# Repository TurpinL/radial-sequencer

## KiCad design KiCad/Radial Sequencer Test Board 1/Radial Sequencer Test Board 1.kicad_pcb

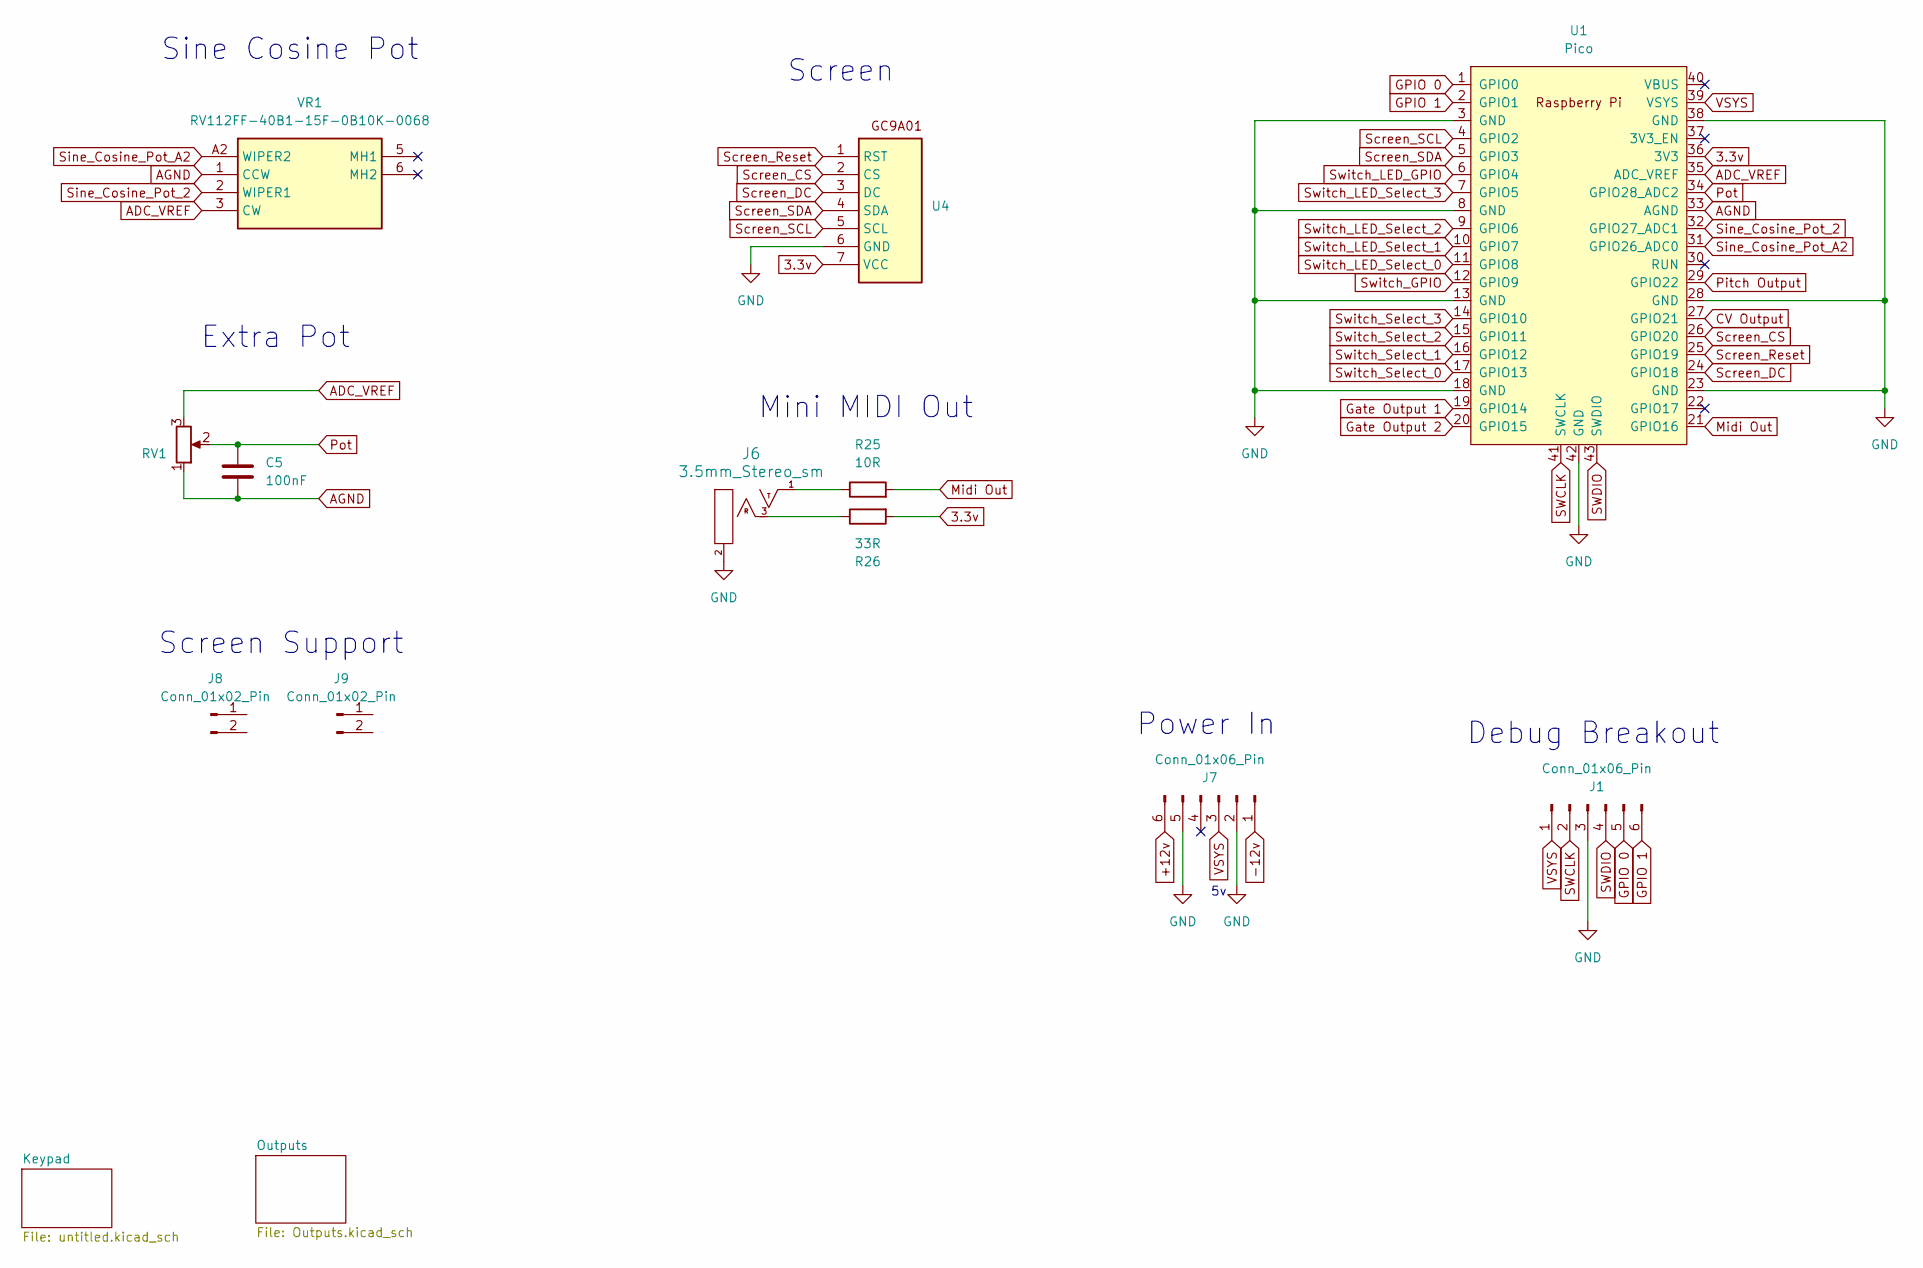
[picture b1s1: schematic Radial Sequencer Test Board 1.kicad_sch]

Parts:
C5: 100nF; C_0805_2012Metric_Pad1.18x1.45mm_HandSolder
J1, J7: Conn_01x06_Pin; PinHeader_1x06_P2.54mm_Vertical
J6: 3.5mm_Stereo_sm; EighthInch_Stereo_PJ366ST; Part Number WQP-WQP518MA
J8, J9: Conn_01x02_Pin; PinHeader_1x02_P2.00mm_Vertical
R25: 10R; R_0805_2012Metric_Pad1.20x1.40mm_HandSolder
R26: 33R; R_0805_2012Metric_Pad1.20x1.40mm_HandSolder
RV1: R_Potentiometer; Potentiometer_Alpha_RD901F-40-00D_Single_Vertical
U1: Pico; RPi_Pico_SMD_TH
U4: PinHeader_1x07_P2.00mm_Vertical
VR1: RV112FF-40B1-15F-0B10K-0068; RV112FF40B115F0B20K0068; Mouser Part Number 317-1240FF-15F-0B20K

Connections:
3.3v: R26.2, U1.36 (3V3), U4.7 (VCC); also elsewhere on the board
+12v: J7.6; also elsewhere on the board
-12v: J7.1; also elsewhere on the board
ADC_VREF: RV1.3, U1.35 (ADC_VREF), VR1.3 (CW)
AGND: C5.2, RV1.1, U1.33 (AGND), VR1.1 (CCW)
CV Output: U1.27 (GPIO21); also elsewhere on the board
GND: J1.3, J6.2 (SHEILD), J7.2, J7.5, U1.3 (GND), U1.8 (GND), U1.13 (GND), U1.18 (GND), U1.23 (GND), U1.28 (GND), U1.38 (GND), U1.42 (GND), U4.6 (GND); also elsewhere on the board
GPIO 0: J1.5, U1.1 (GPIO0)
GPIO 1: J1.6, U1.2 (GPIO1)
Gate Output 1: U1.19 (GPIO14); also elsewhere on the board
Gate Output 2: U1.20 (GPIO15); also elsewhere on the board
Midi Out: R25.2, U1.21 (GPIO16)
unnamed: J6.1 (SIG), R25.1
unnamed: J6.3 (SW), R26.1
Pitch Output: U1.29 (GPIO22); also elsewhere on the board
Pot: C5.1, RV1.2, U1.34 (GPIO28_ADC2)
SWCLK: J1.2, U1.41 (SWCLK)
SWDIO: J1.4, U1.43 (SWDIO)
Screen_CS: U1.26 (GPIO20), U4.2 (CS)
Screen_DC: U1.24 (GPIO18), U4.3 (DC)
Screen_Reset: U1.25 (GPIO19), U4.1 (RST)
Screen_SCL: U1.4 (GPIO2), U4.5 (SCL)
Screen_SDA: U1.5 (GPIO3), U4.4 (SDA)
Sine_Cosine_Pot_2: U1.32 (GPIO27_ADC1), VR1.2 (WIPER1)
Sine_Cosine_Pot_A2: U1.31 (GPIO26_ADC0), VR1.A2 (WIPER2)
Switch_GPIO: U1.12 (GPIO9); also elsewhere on the board
Switch_LED_GPIO: U1.6 (GPIO4); also elsewhere on the board
Switch_LED_Select_0: U1.11 (GPIO8); also elsewhere on the board
Switch_LED_Select_1: U1.10 (GPIO7); also elsewhere on the board
Switch_LED_Select_2: U1.9 (GPIO6); also elsewhere on the board
Switch_LED_Select_3: U1.7 (GPIO5); also elsewhere on the board
Switch_Select_0: U1.17 (GPIO13); also elsewhere on the board
Switch_Select_1: U1.16 (GPIO12); also elsewhere on the board
Switch_Select_2: U1.15 (GPIO11); also elsewhere on the board
Switch_Select_3: U1.14 (GPIO10); also elsewhere on the board
VSYS: J1.1, J7.3, U1.39 (VSYS)

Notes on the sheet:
Power In
Mini MIDI Out
Debug Breakout
Screen
Screen Support
Extra Pot
Sine Cosine Pot

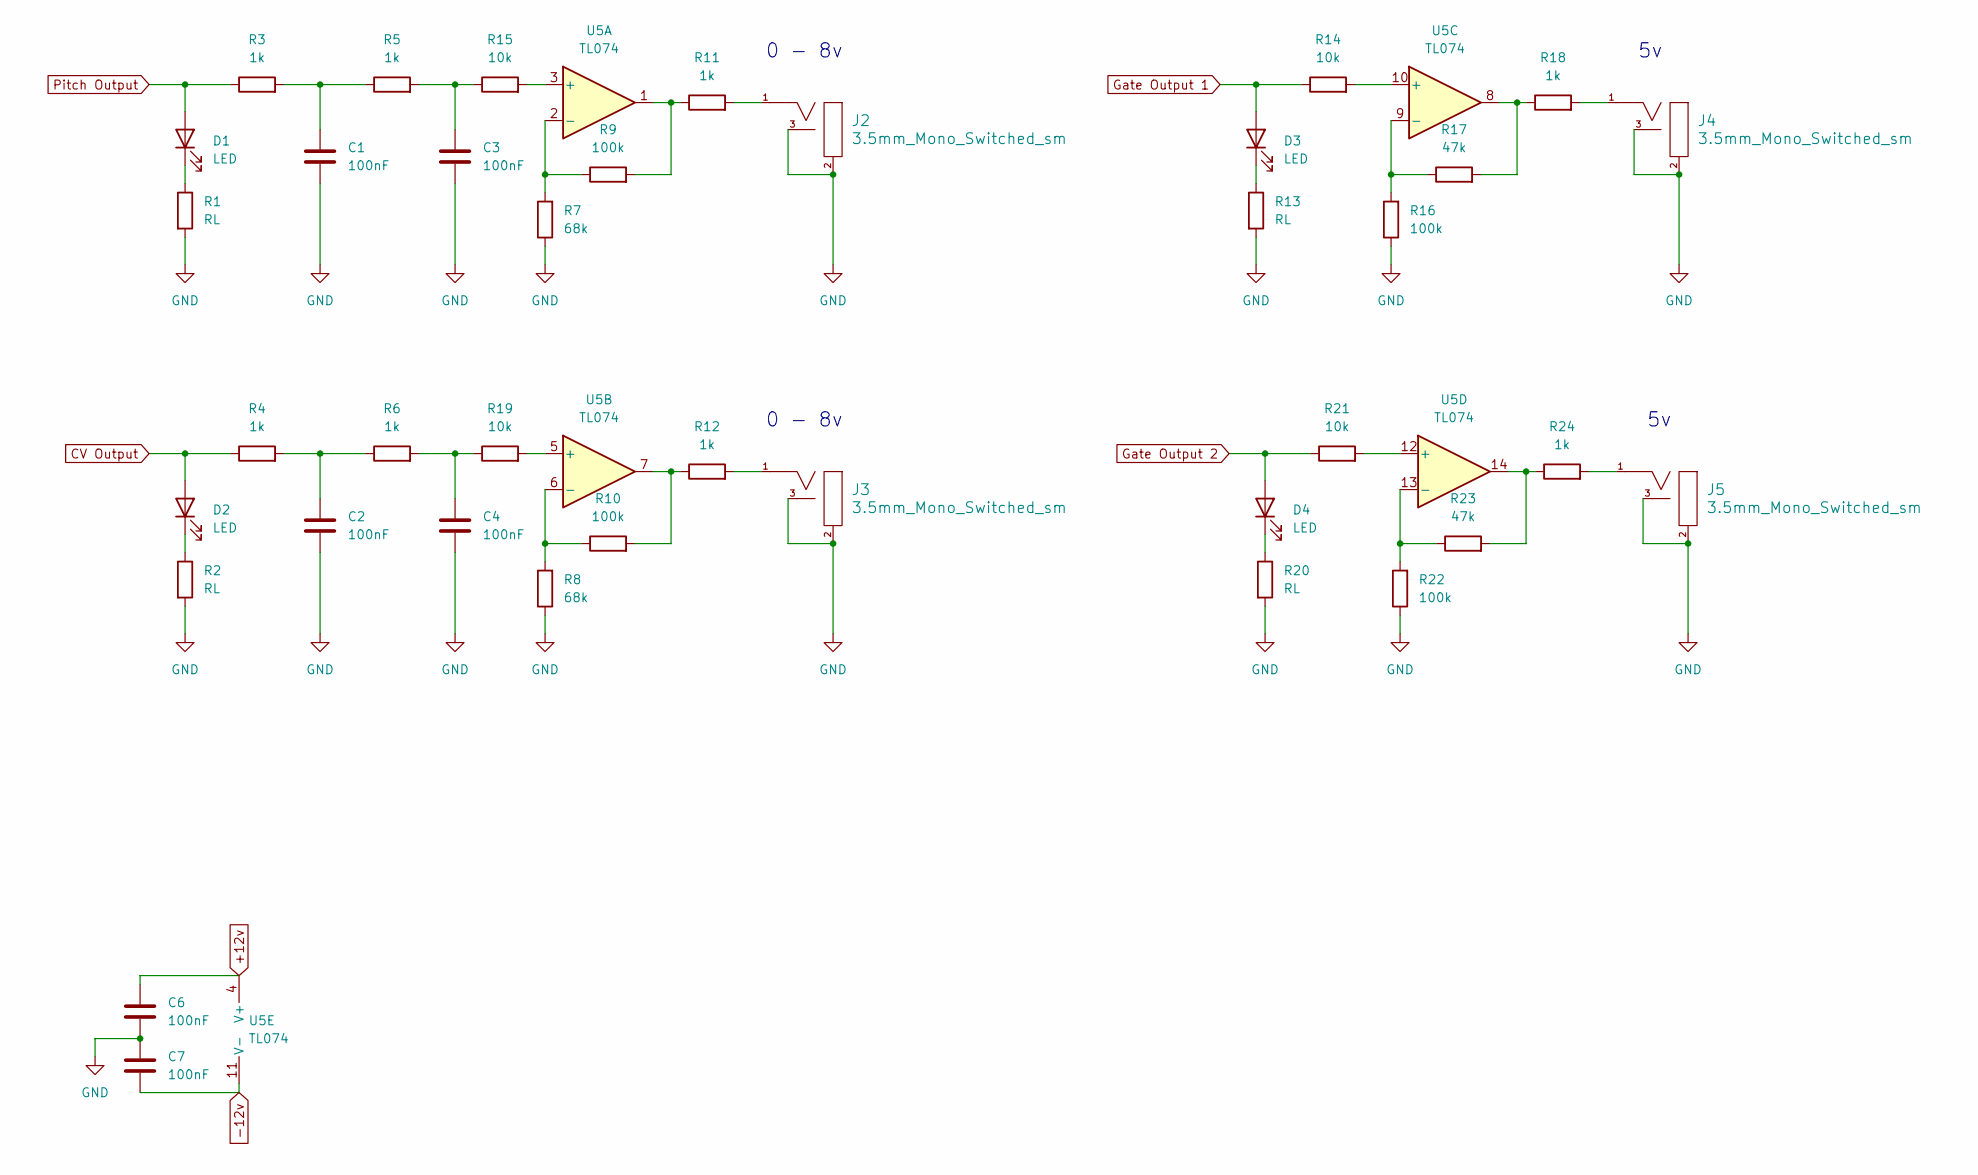
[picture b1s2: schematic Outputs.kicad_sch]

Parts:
C1, C2, C3, C4, C6, C7: 100nF; C_0805_2012Metric_Pad1.18x1.45mm_HandSolder
D1, D2, D3, D4: LED; LED_D3.0mm
J2, J3, J4, J5: 3.5mm_Mono_Switched_sm; EighthInch_PJ398SM; Part Number WQP-WQP518MA
R1, R2, R13, R20: RL; R_0805_2012Metric_Pad1.20x1.40mm_HandSolder
R3, R4, R5, R6, R11, R12, R18, R24: 1k; R_0805_2012Metric_Pad1.20x1.40mm_HandSolder
R7, R8: 68k; R_0805_2012Metric_Pad1.20x1.40mm_HandSolder
R9, R10, R16, R22: 100k; R_0805_2012Metric_Pad1.20x1.40mm_HandSolder
R14, R15, R19, R21: 10k; R_0805_2012Metric_Pad1.20x1.40mm_HandSolder
R17, R23: 47k; R_0805_2012Metric_Pad1.20x1.40mm_HandSolder
U5: TL074; SOIC-14_3.9x8.7mm_P1.27mm

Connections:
+12v: C6.1, U5.4 (V+); also elsewhere on the board
-12v: C7.2, U5.11 (V-); also elsewhere on the board
CV Output: D2.2 (A), R4.1; also elsewhere on the board
GND: C1.2, C2.2, C3.2, C4.2, C6.2, C7.1, J2.2 (SHEILD), J2.3 (SW), J3.2 (SHEILD), J3.3 (SW), J4.2 (SHEILD), J4.3 (SW), J5.2 (SHEILD), J5.3 (SW), R1.2, R2.2, R7.1, R8.1, R13.2, R16.1, R20.2, R22.1; also elsewhere on the board
Gate Output 1: D3.2 (A), R14.1; also elsewhere on the board
Gate Output 2: D4.2 (A), R21.1; also elsewhere on the board
unnamed: C1.1, R3.2, R5.1
unnamed: C2.1, R4.2, R6.1
unnamed: C3.1, R5.2, R15.1
unnamed: C4.1, R6.2, R19.1
unnamed: D1.1 (K), R1.1
unnamed: D2.1 (K), R2.1
unnamed: D3.1 (K), R13.1
unnamed: D4.1 (K), R20.1
unnamed: J2.1 (SIG), R11.2
unnamed: J3.1 (SIG), R12.2
unnamed: J4.1 (SIG), R18.2
unnamed: J5.1 (SIG), R24.2
unnamed: R10.2, R12.1, U5.7
unnamed: R9.2, R11.1, U5.1
unnamed: R17.2, R18.1, U5.8
unnamed: R23.2, R24.1, U5.14
unnamed: R15.2, U5.3 (+)
unnamed: R7.2, R9.1, U5.2 (-)
unnamed: R19.2, U5.5 (+)
unnamed: R8.2, R10.1, U5.6 (-)
unnamed: R14.2, U5.10 (+)
unnamed: R16.2, R17.1, U5.9 (-)
unnamed: R21.2, U5.12 (+)
unnamed: R22.2, R23.1, U5.13 (-)
Pitch Output: D1.2 (A), R3.1; also elsewhere on the board

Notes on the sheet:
0 - 8v

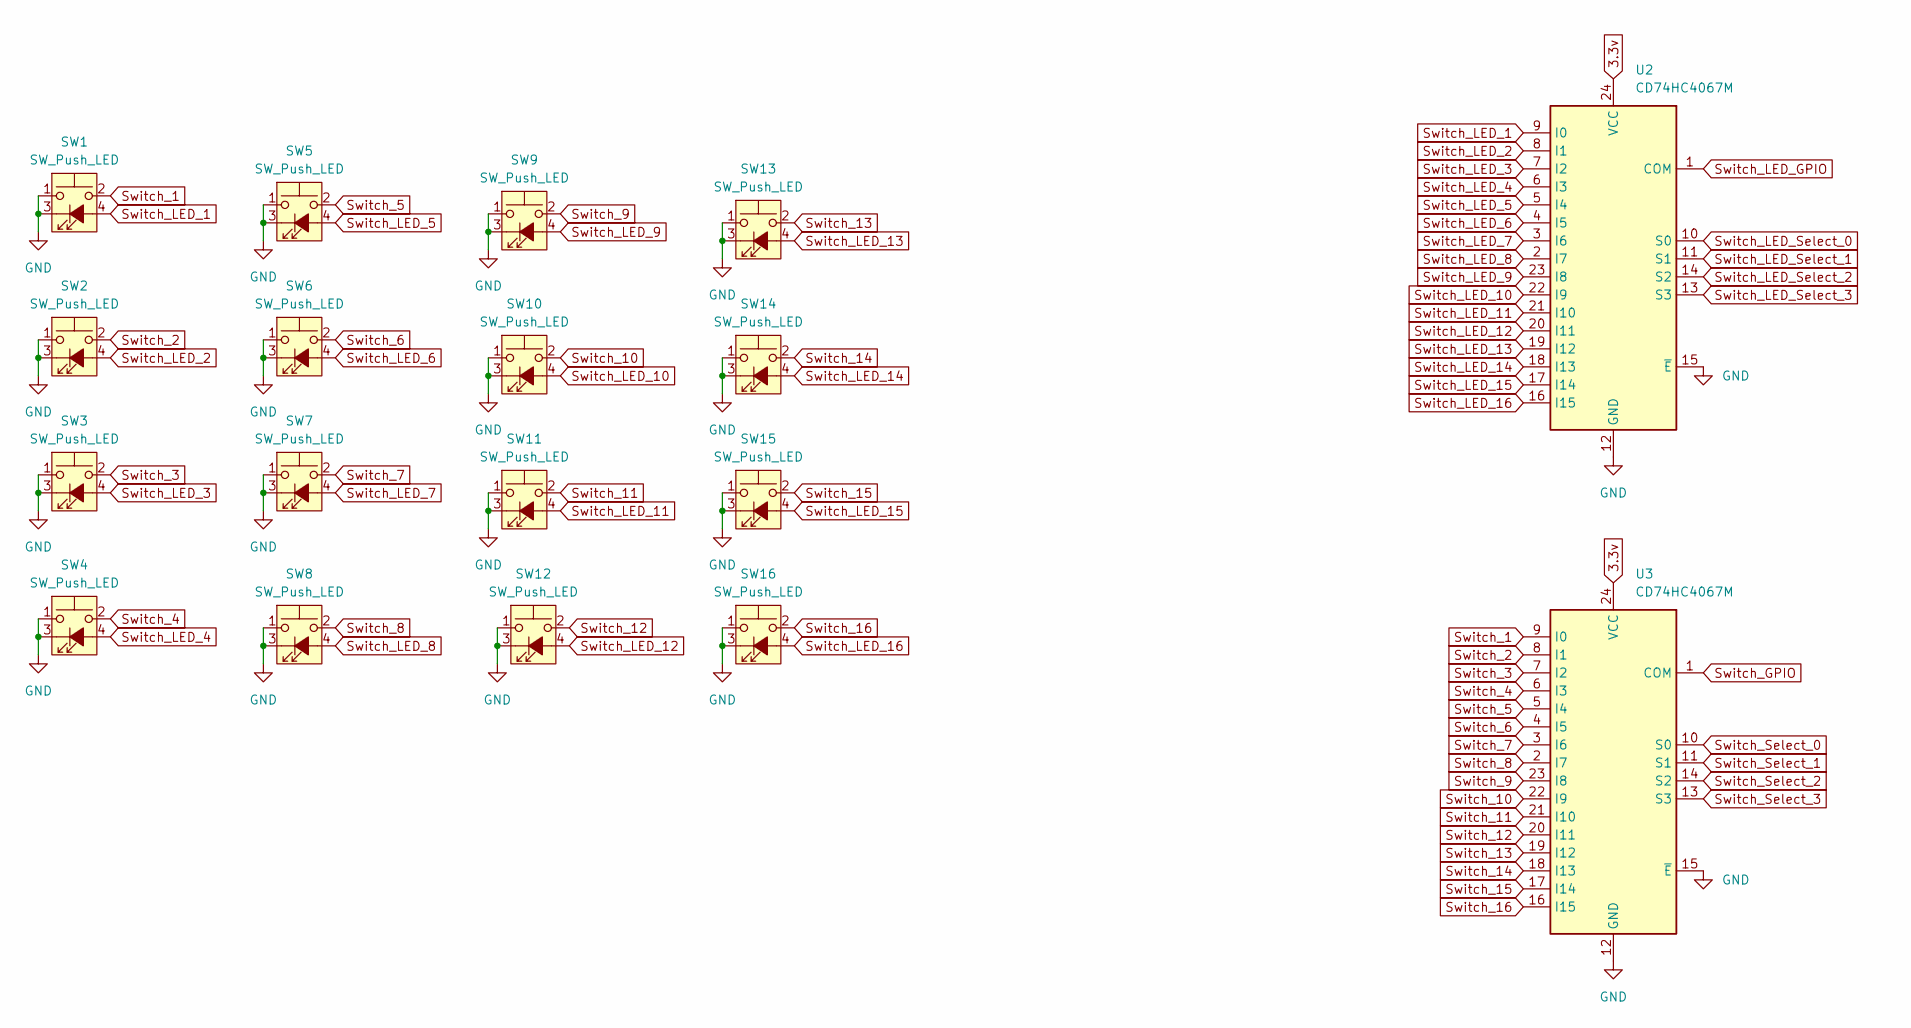
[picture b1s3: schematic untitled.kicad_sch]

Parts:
SW1, SW2, SW3, SW4, SW5, SW6, SW7, SW8, SW9, SW10, SW11, SW12, SW13, SW14, SW15, SW16: SW_Push_LED; Low_Profile_LED_Button
U2, U3: CD74HC4067M; SOIC-24W_7.5x15.4mm_P1.27mm

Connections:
3.3v: U2.24 (VCC), U3.24 (VCC); also elsewhere on the board
GND: SW1.1, SW1.3 (K), SW2.1, SW2.3 (K), SW3.1, SW3.3 (K), SW4.1, SW4.3 (K), SW5.1, SW5.3 (K), SW6.1, SW6.3 (K), SW7.1, SW7.3 (K), SW8.1, SW8.3 (K), SW9.1, SW9.3 (K), SW10.1, SW10.3 (K), SW11.1, SW11.3 (K), SW12.1, SW12.3 (K), SW13.1, SW13.3 (K), SW14.1, SW14.3 (K), SW15.1, SW15.3 (K), SW16.1, SW16.3 (K), U2.12 (GND), U2.15 (~E), U3.12 (GND), U3.15 (~E); also elsewhere on the board
Switch_1: SW1.2, U3.9 (I0)
Switch_2: SW2.2, U3.8 (I1)
Switch_3: SW3.2, U3.7 (I2)
Switch_4: SW4.2, U3.6 (I3)
Switch_5: SW5.2, U3.5 (I4)
Switch_6: SW6.2, U3.4 (I5)
Switch_7: SW7.2, U3.3 (I6)
Switch_8: SW8.2, U3.2 (I7)
Switch_9: SW9.2, U3.23 (I8)
Switch_10: SW10.2, U3.22 (I9)
Switch_11: SW11.2, U3.21 (I10)
Switch_12: SW12.2, U3.20 (I11)
Switch_13: SW13.2, U3.19 (I12)
Switch_14: SW14.2, U3.18 (I13)
Switch_15: SW15.2, U3.17 (I14)
Switch_16: SW16.2, U3.16 (I15)
Switch_GPIO: U3.1 (COM); also elsewhere on the board
Switch_LED_1: SW1.4 (A), U2.9 (I0)
Switch_LED_2: SW2.4 (A), U2.8 (I1)
Switch_LED_3: SW3.4 (A), U2.7 (I2)
Switch_LED_4: SW4.4 (A), U2.6 (I3)
Switch_LED_5: SW5.4 (A), U2.5 (I4)
Switch_LED_6: SW6.4 (A), U2.4 (I5)
Switch_LED_7: SW7.4 (A), U2.3 (I6)
Switch_LED_8: SW8.4 (A), U2.2 (I7)
Switch_LED_9: SW9.4 (A), U2.23 (I8)
Switch_LED_10: SW10.4 (A), U2.22 (I9)
Switch_LED_11: SW11.4 (A), U2.21 (I10)
Switch_LED_12: SW12.4 (A), U2.20 (I11)
Switch_LED_13: SW13.4 (A), U2.19 (I12)
Switch_LED_14: SW14.4 (A), U2.18 (I13)
Switch_LED_15: SW15.4 (A), U2.17 (I14)
Switch_LED_16: SW16.4 (A), U2.16 (I15)
Switch_LED_GPIO: U2.1 (COM); also elsewhere on the board
Switch_LED_Select_0: U2.10 (S0); also elsewhere on the board
Switch_LED_Select_1: U2.11 (S1); also elsewhere on the board
Switch_LED_Select_2: U2.14 (S2); also elsewhere on the board
Switch_LED_Select_3: U2.13 (S3); also elsewhere on the board
Switch_Select_0: U3.10 (S0); also elsewhere on the board
Switch_Select_1: U3.11 (S1); also elsewhere on the board
Switch_Select_2: U3.14 (S2); also elsewhere on the board
Switch_Select_3: U3.13 (S3); also elsewhere on the board

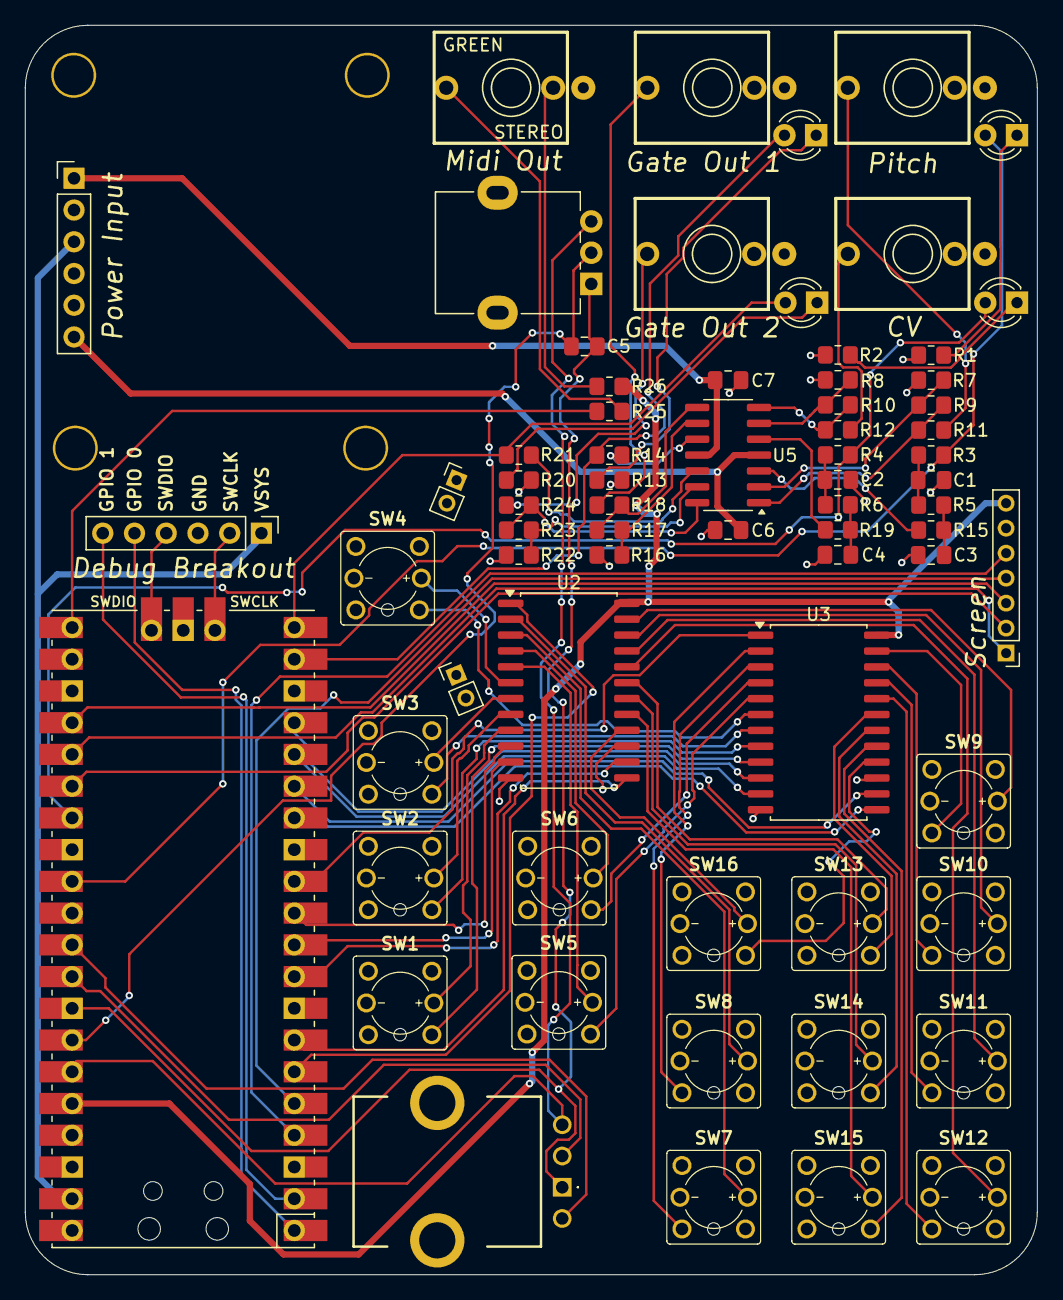
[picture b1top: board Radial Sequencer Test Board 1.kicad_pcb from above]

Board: 2 copper layers, 81.0 x 100.0 mm, 69 parts (0 on the bottom side), 92 nets.

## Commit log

2024-07-27 Fresh PlatformIO project
2024-07-27 Basic screen functionality
2024-07-28 Basic sequence
2024-07-29 Added the beat
2024-08-04 Pulse count
2024-08-05 Futsing
2024-08-05 Faster pulse pip drawing
2024-08-09 Implemented gate modes
2024-08-15 Skip
2024-08-19 Updated Strike-Through
2024-08-19 Better button handling
2024-08-20 Always progress the beat indicator clockwise
2024-08-25 Selection
2024-08-26 Gate handles held and skipped pulses Beat indicator improvements Gate and Pitch LEDs More buttons
2024-08-26 Tracked disabled pulses passing
2024-08-26 Slide!
2024-09-17 Improve input system
2024-09-17 Implement pulse count and gate mode buttons
2024-11-12 Clone and Delete - Removed hysteresis because it was causing issues with deletion
2024-11-12 Colours - Added a new colour to indicate user interaction
2024-12-13 Position animation
2025-01-03 Gate mode config animation
2025-01-04 Use earlphilhower core
2025-01-04 Upgrade to Pico 2
    Buttons needed to be changed to pull-up to work around an bug with the pico 2
2025-02-18 Big commit, oops * Prototype PCB v1 * Midi output * Move * Picoprobe
2025-03-03 Multiplexed Buttons and button LEDs
2025-04-09 Change how the stage value is drawn
2025-05-04 Undo redo
2025-05-05 Improved Animations
2025-05-10 Extract pulse pip button handling logic to it's own class
2025-05-16 Refactoring, separating button handlers out into their own files
2025-05-19 Refactoring: Polymorphic button handling
2025-05-19 Refactor: Move rendering code out of main
2025-05-28 Move yet more code out of main
2025-06-05 Basic arpeggiation implementation
2025-06-28 Move stage to it's own file
2025-06-29 Implement a second screen buffer
2025-06-30 Bugfix: BPM was jittering, causing gate to jitter on and off at the thresholds causing midi notes to be constantly retriggered
2025-07-12 Tweak Highlight behaviour
2025-07-12 Mutation rough draft
2025-07-16 Piano based pitch selection indicator
2025-08-04 Quantizer
2025-08-12 Fixed colliding IDs
2025-08-12 More strict button debouncing
2025-08-17 Render the currently played note
2025-08-17 Fixed VS Code complaining about the utils import
2025-08-17 Diminuified FPS display
2025-08-17 Refactor lerpColour
2025-08-20 Focused on muting and single pulse stages instead of gate mode and pulse count
2025-08-20 Decoupled Button class from Commands
